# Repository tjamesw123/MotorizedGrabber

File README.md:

# MotorizedGrabber
3d models, custom circuit board, design and parts list for a motorized grabber design

# Grabber Shopping List

2 mm outer thickness with 22 mm inner diameter alumuinum pipe, 2 meters 

3d printer and filament, carbon fiber PLA was used for this grabber but normal PLA should still work with possibly some tweaks to the models or maybe non at all as Carbon Fiber PLA and PLA have similar print characteristics
(Note that a sleve was used for fitting the adapter to the alumnium grabber pipe better after the lathe was used to trim the part till it fit with the alumium pipe, there is almost certainly another way to fit the aluminum pipe and the part together without such equipment. I would suggest tuning the fitting parts of the prints inner and outer diameter sizes till you can print a part that fits well with the aluminium pipe without any trim)

Drill Batterys and Charger https://www.amazon.com/dp/B07X2V5116/?coliid=I2IH57A649QSUQ&colid=3JNOTM74GBT0X&psc=1&ref_=list_c_wl_lv_ov_lig_dp_it

Round Head Machine Screw, 8-32-Inch x 1-Inch, 2 of them https://www.amazon.com/dp/B00843ER7W?ref_=cm_sw_r_cp_ud_dp_5XYYPG3079ASXCVBMPT5

Small Screws https://www.amazon.com/dp/B078ZVLFWY?_encoding=UTF8&ref=cm_sw_r_cp_ud_dp_73YYQMXGK250FDRDGENX&ref_=cm_sw_r_cp_ud_dp_73YYQMXGK250FDRDGENX&social_share=cm_sw_r_cp_ud_dp_73YYQMXGK250FDRDGENX&th=1

Micro Limit Switch	https://www.amazon.com/dp/B07X142VGC/?coliid=I23S51OHWOTIJK&colid=3JNOTM74GBT0X&psc=1&ref_=list_c_wl_lv_ov_lig_dp_it , I got the 10 pack of these but most limit switches will do as you only need one of them for the limiter

SPDT Push Button Switches https://www.digikey.com/en/products/detail/e-switch/700SP7B10M2QEH/502058 , I bought 4 when making it in case I messed up 2 but you only need 2 for the design

Custom Circuit Board for Grabber , The gerber files are in the repo, I used PCBWay for ordering the boards, you do have to mininum order 10 for 20 dollars but for this project it made soldering way easier and much more reliable then soldering directly to the pins.

A fair amount of 22 gage wire, I made an attempt at using quick connects to make the battery connection to the switches easier to disconnect but the current space issues make such things mildly difficult so you can just directly wire up the grabber and desolder for repairs. Annoying but with the space constraints it made sense at the time.

There are about 4 separate runs of wire you will have to run other then the wires built into the linear actuator
There are circuit diagrams that you can view from the photo section of the layout of the switch board or if you feel like not using it, it's going to tell you exactly how you have to run things.

Grabber 48"	https://www.amazon.com/dp/B000RUKZNU?ref=ppx_yo2ov_dt_b_fed_asin_title&th=1 , this is the grabber that you need to basically need to cut and then combined with the other parts in this design
Or
Grabber 36" https://www.amazon.com/dp/B0000V0AGS/?coliid=I2SN9CFSNLCHWP&colid=3JNOTM74GBT0X&psc=1&ref_=list_c_wl_lv_ov_lig_dp_it , another grabber you can use if you want a shorter grabber for whatever reason, still works out the same for the most part

Battery Prongs	https://www.te.com/en/product-42214-2.html?te_bu=Cor&te_type=srch&te_campaign=ggl_usa_cor-ggl-usa-srch-fy23-smbmktg-pfm-emi-us_sma-2844_2&elqCampaignId=163125&gclid=Cj0KCQiAwJWdBhCYARIsAJc4idDtBZFJZNP_-SDxGzrRgCFeqgtEI1sV-STMod0eMnQQOVzPxxeOGPUaAlAhEALw_wcB , I bought 4 again also because I wanted backups but you only need 2\

Micro Linear Actuator https://www.amazon.com/dp/B0B9JPQDSV?ref=ppx_yo2ov_dt_b_fed_asin_title&th=1, I bought 1 of these
(The gearing here is more aggressive then it needs to be on the 36" grabber but for the 48" it is required to get one of these as the gearing for a faster motor doesn't have enough static friction to keep the spring on the grabber from moving)

### An addendum on the PCB
You technically don't need this thing if your really determined but trust me when I say it really can be scuffed if you don't get this, if you are a beginner solderer I would recommend this and honestly even if your more experienced it just makes the whole circuit a lot neater. Having tiny 22 gage wires running inbetween the pins is messy, I rest my case. I have like 7 spares at this moment in time so if your really determined to not order a fresh batch you can attempt to reach out. The dupes also leave room for failures and they make for ok solder practice boards as well with the number of pins.

The spacing is also tiny there isn't a lot of room in the handle of the grabber so the board just made sense to keep things more neat

## Photos

(I used KiCAD for the board designing program)
[GerbersAndProductionFiles](SwitchBoard/pcbway_production)
Also use the settings listed in the [GrabberPCBSpecs](GrabberPCBSpecs.pdf)

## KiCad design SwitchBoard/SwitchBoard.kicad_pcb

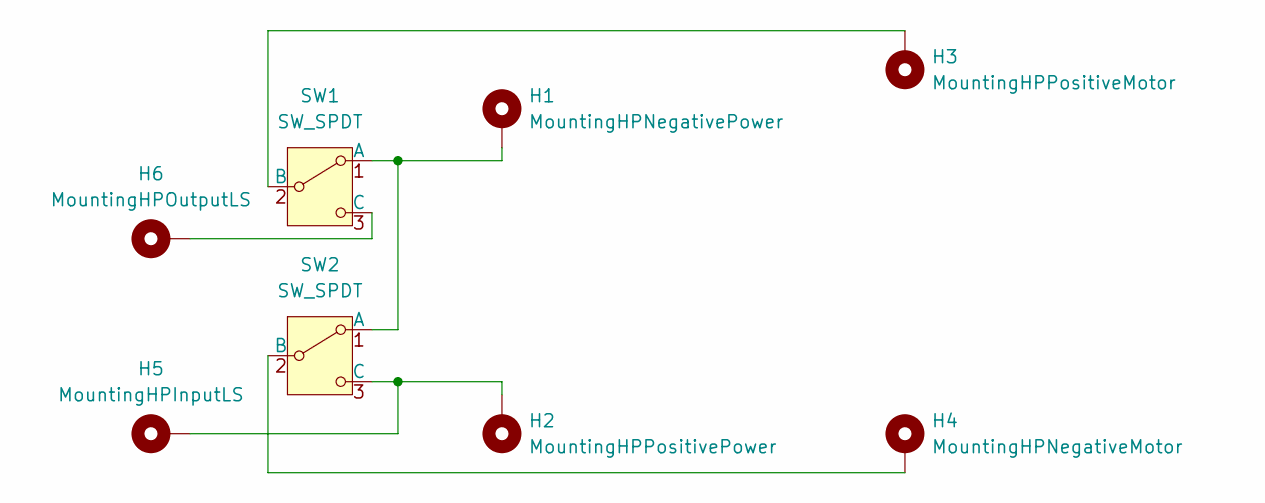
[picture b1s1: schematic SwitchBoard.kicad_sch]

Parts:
H1: MountingHPNegativePower; SmallerPad
H2: MountingHPPositivePower; SmallerPad
H3: MountingHPPositiveMotor; SmallerPad
H4: MountingHPNegativeMotor; SmallerPad
H5: MountingHPInputLS; SmallerPad
H6: MountingHPOutputLS; SmallerPad
SW1, SW2: SW_SPDT; SP-7

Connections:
unnamed: H1.1, SW1.1 (A), SW2.1 (A)
unnamed: H3.1, SW1.2 (B)
unnamed: H6.1, SW1.3 (C)
unnamed: H4.1, SW2.2 (B)
unnamed: H2.1, H5.1, SW2.3 (C)

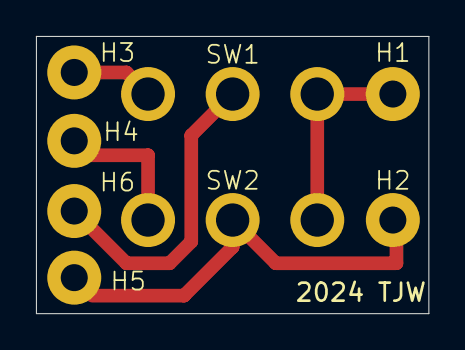
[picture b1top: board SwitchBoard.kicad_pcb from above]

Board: 2 copper layers, 21.8 x 15.4 mm, 8 parts (0 on the bottom side), 5 nets.

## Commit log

2025-03-30 Added resources
2025-03-30 Updated README.md, and started adding things in
2025-03-30 Edited README.md
2025-03-30 Reorganized stls and blender files
2025-03-30 Fixed the part list
